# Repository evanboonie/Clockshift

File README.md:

# Clockshift
Vairable clock generator that fits into a 14-DIP oscillator socket. Also includes a 8-DIP/4-SOJ adapter with optional 4-SOJ disable switch. Primairly intended for overclocking old computers.

## DigiKey Sourcing
Here is a [shared list on DigiKey](https://www.digikey.com/en/mylists/list/JQZCK1QVDC) to help simplify component sourcing.

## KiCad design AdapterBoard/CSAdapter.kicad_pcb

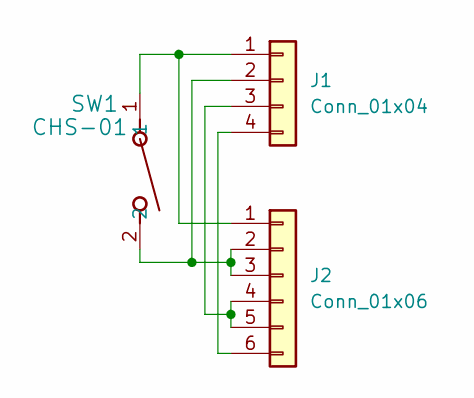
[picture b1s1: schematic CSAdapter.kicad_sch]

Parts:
J1: Conn_01x04; PinHeader_2x07_4pop_P2.54mmX7.62mm_Vertical
J2: Conn_01x06; PinHeader_2x04_6pop_P2.54mmX7.62mm_Vertical
SW1: CHS-01; CHS-01B_NDC

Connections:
unnamed: J1.1, J2.1, SW1.1
unnamed: J1.2, J2.2, J2.3, SW1.2
unnamed: J1.3, J2.4, J2.5
unnamed: J1.4, J2.6

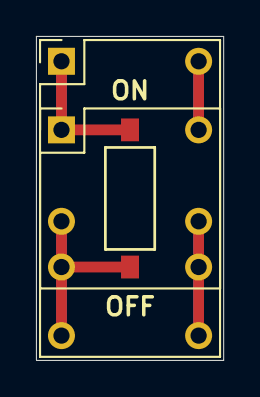
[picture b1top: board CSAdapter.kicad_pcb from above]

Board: 2 copper layers, 10.4 x 18.0 mm, 3 parts (0 on the bottom side), 4 nets.

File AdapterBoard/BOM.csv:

"Reference","Value","Datasheet","Footprint","Qty","DNP"
"J1","1107741","https://www.arieselec.com/wp-content/uploads/2020/02/14005-o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","14-DIP","1",""
"J2","220-1-08-003","https://www.cnctech.us/pdfs/220-1-XX-00X_.pdf","8-DIP","1",""
"SW1","CHS-01TB","https://www.nidec-components.com/e/catalog/switch/chs.pdf","Custom Gull Wing","1",""

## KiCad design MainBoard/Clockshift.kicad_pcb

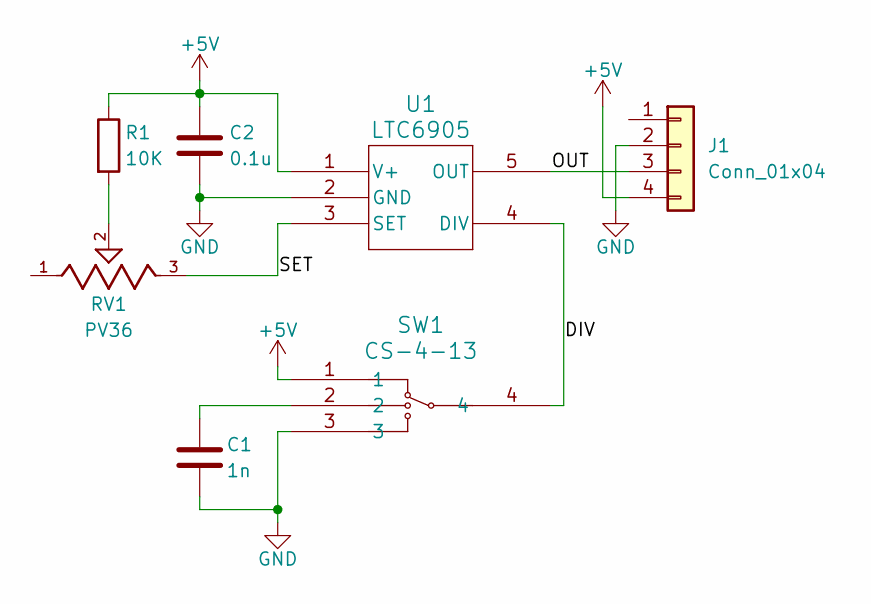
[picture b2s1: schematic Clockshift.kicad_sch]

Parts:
C1: 1n; C_0603_1608Metric_Pad1.08x0.95mm_HandSolder
C2: 0.1u; C_0603_1608Metric_Pad1.08x0.95mm_HandSolder
J1: Conn_01x04; PinHeader_2x07_4pop_P2.54mmX7.62mm_Vertical
R1: 10K; R_0603_1608Metric_Pad0.98x0.95mm_HandSolder
RV1: PV36; SM-3W
SW1: CS-4-13; CS-4-13NA_NDC
U1: LTC6905; S_5_ADI

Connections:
+5V: C2.1, J1.4, R1.1, SW1.1, U1.1 (V+)
/DIV: SW1.4, U1.4 (DIV)
/OUT: J1.3, U1.5 (OUT)
/SET: RV1.3, U1.3 (SET)
GND: C1.2, C2.2, J1.2, SW1.3, U1.2 (GND)
unnamed: C1.1, SW1.2
unnamed: R1.2, RV1.2

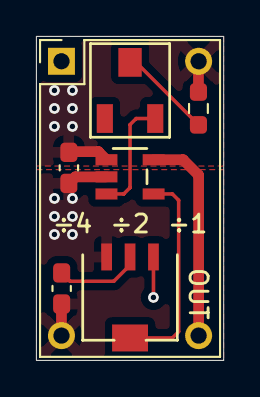
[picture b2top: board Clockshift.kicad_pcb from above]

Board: 4 copper layers, 10.4 x 18.0 mm, 7 parts (0 on the bottom side), 7 nets.

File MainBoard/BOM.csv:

"Reference","Value","Datasheet","Footprint","Qty","DNP"
"C1","1n","https://mm.digikey.com/Volume0/opasdata/d220001/medias/docus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","0603","1",""
"C2","0.1u","https://mm.digikey.com/Volume0/opasdata/d220001/medias/docus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","0603","1",""
"J1","220-1-14-003","https://www.cnctech.us/pdfs/220-1-XX-00X_.pdf","14-DIP","1",""
"R1","10K","https://api.pim.na.industrial.panasonic.com/file_stream/main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","0603","1",""
"RV1","SM-3TW203","https://www.nidec-components.com/e/catalog/trimmer/sm-3&sm-31.pdf","Custom J Lead","1",""
"SW1","CS-4-13NTA","https://www.nidec-components.com/e/catalog/switch/cs-4.pdf","Custom J Lead","1",""
"U1","LTC6905","https://www.analog.com/media/en/technical-documentation/data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","SOT-23-5","1",""

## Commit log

2024-12-10 license
2024-12-10 Ignore DS Store
2024-12-11 Adding initial libs, schematics, and boards
2024-12-11 Adding BOM
2024-12-11 Design rules and gerber files
2024-12-11 Ignore zipped gerber files
2024-12-11 Fix adapter board for dual layer
